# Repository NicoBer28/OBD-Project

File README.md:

# OBD-C

OBD-C is a car assistant and real-time analysis platform built around a
custom OBD-II Bluetooth dongle. A family (or a car-rental fleet) shares one
or more cars; the app tracks who's driving and where, splits fuel cost, and
surfaces real-time and historical vehicle data collected by the hardware.

## Features

- Division of fuel cost among multiple users
- Real-time vehicle diagnostics and driving-behavior feedback
- Fuel efficiency tracking, maintenance reminders and alerts
- Trip history and last-parked location
- Compatibility with a wide range of vehicles that support OBD-II

## Repository layout

This is a monorepo with three buildable pieces plus the hardware design:

| Path | What it is | Start here |
|---|---|---|
| `app/` | Flutter app (iOS/Android/desktop) — the user-facing client | [`app/obd_app/README.md`](app/obd_app/README.md) |
| `api/` | Spring Boot backend — auth, cars, groups, trips, telemetry | [`api/README.md`](api/README.md) · [`api/ROADMAP.md`](api/ROADMAP.md) |
| `hardware/` | ESP32 firmware — BLE + OBD-II/CAN bus reading | [`hardware/README.md`](hardware/README.md) |
| `circuito/` | KiCad schematic/PCB for the OBD dongle | — |

## Architecture at a glance

The Flutter UI is a "dumb" reactive layer: it doesn't touch Bluetooth or
GPS, it just listens to an event channel and draws. A native foreground
service (Kotlin on Android, Swift on iOS) owns the BLE/GPS connection and
survives the UI being killed, so a trip keeps recording with the phone in a
pocket. The ESP32 dongle only speaks BLE, so **the phone is the relay** —
it batches readings and uploads them to the API, which is built to make
retrying a batch always safe. Full reasoning: [`docs/architecture.md`](docs/architecture.md).
System diagram (Structurizr C4 model): [`docs/C4 diagram`](<docs/C4 diagram>).

## Getting started

- **App** — Flutter setup: [`app/obd_app/README.md`](app/obd_app/README.md).
  Building for iOS needs one extra per-developer step:
  [`docs/ios-setup.md`](docs/ios-setup.md).
- **API** — needs Postgres and a couple of env vars:
  [`api/README.md`](api/README.md).
- **Firmware** — ESP-IDF via Docker/Dev Containers:
  [`hardware/README.md`](hardware/README.md).

## Development workflow

- **Branching**: GitFlow — see [`docs/flow.md`](docs/flow.md).
- **Commits**: [Conventional Commits](https://www.conventionalcommits.org/),
  enforced by a `commit-msg` hook (`feat`, `fix`, `docs`, `chore`, …).
- **One-time setup**: `make setup` installs the git hooks (lefthook +
  `.githooks`).
- **Before pushing**: `make format` (dart + clang-format) and `make check`
  (format check, `flutter analyze`, `flutter test`).
- CI (`.github/workflows/ci.yaml`) currently only guards that `README.md`
  and `docs/` exist; extend it here as the app/firmware test suites grow
  (the API already runs its own suite via `./mvnw test`, see
  [`api/README.md`](api/README.md#testing)).

## Docs index

| Doc | Contents |
|---|---|
| [`docs/flow.md`](docs/flow.md) | Git branching model (GitFlow) |
| [`docs/architecture.md`](docs/architecture.md) | Architecture decisions and rationale — background telemetry, native bridge, Pigeon, BLE pitfalls |
| [`docs/funcionalities.md`](docs/funcionalities.md) | Feature brainstorm/spec: sharing, historical data, notifications, B2B |
| [`docs/C4 diagram`](<docs/C4 diagram>) | C4 model (Structurizr) of the system |
| [`docs/ios-setup.md`](docs/ios-setup.md) | Per-developer iOS signing setup, and how to build/run on iOS |

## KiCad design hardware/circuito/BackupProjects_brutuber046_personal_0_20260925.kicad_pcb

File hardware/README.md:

# OBD-Project: ESP32 Firmware
Entorno de desarrollo de firmware en ESP-IDF utilizando Docker y VS Code Dev Containers.

## ⚙️ Setup del Entorno en Linux

### 1. Instalar Docker y Visual Studio Code. 

- Se puede evitar este último, pero en ese caso hay que abrir una terminal dentro docker para compilar

### 2. Descargar la imagen oficial de espressif
```bash
docker pull espressif/idf:v6.1
```
### 3. Instalar la extensión Dev Containers en VS Code 
- Tambien llamada por ID `ms-vscode-remote.remote-containers`

### 4. Abrir la carpeta raíz del repositorio (OBD-Project) en VS Code

```bash
# desde el directorio previo al repositorio de git
code ./OBD-Project/
# o, desde dentro de OBD-Project
code .
```

### 5. Crear una carpeta llamada `.devcontainer` y adentro crear el archivo `devcontainer.json` con el siguiente contenido
```json
{
  "name": "ESP32 Lab",
  "image": "espressif/idf:latest",
  "runArgs": [
    "--network=host",
    "--privileged"
  ],
  "workspaceFolder": "/workspaces/OBD-Project/hardware",
  "mounts": [
    "source=/dev,target=/dev,type=bind"
  ],
  "customizations": {
    "vscode": {
      "extensions": [
        "ms-vscode.cpptools-extension-pack",
		"usernamehw.errorlens",
		"google.google-antigravity"
      ]
    }
  },
  "postCreateCommand": "echo 'source /opt/esp/idf/export.sh' >> ~/.bashrc"
}

```

### 6. Presionar F1, escribir Dev Containers: Reopen in Container y presionar Enter (o usar el botón inferior derecho).
- Se va a abrir dentro de la carpeta hardware, esto es para facilitar el workflow
## 🛠️ Build & Flash
### 1. Con el contenedor ya cargado, abrir una nueva terminal integrada en VS Code
- Se va a abrir una terminal dentro del contenedor

### 2. Seleccionar modelo de ESP y transceptor:
```bash
./set_driver.sh <transceptor> <modelo>
```
- Modelo puede ser `esp32`, `esp32-c3` o cualquier modelo compatible con las funcionalidades (tomar en cuenta la implementación en simple o multinúcleo de las tareas en FreeRTOS)
- Transceptor puede ser `twai` o `mcp`
### 3. Para compilar:
```bash
idf.py build
```
- Se van a descargar todas las dependencias del proyecto
### 4. La libreria del mcp2515 utilizada tiene un error de dependencias en su `CMakeLists.txt`. Para corregirlo ejecutar, desde el directorio actual:

```bash
echo "idf_component_register(SRCS "mcp2515.cpp"
                    INCLUDE_DIRS "include"
                    REQUIRES esp_driver_spi)" > ./managed_components/mcp2515/CMakeLists.txt
```
- Tambien se puede editar directamente el archivo
### 5. Flashear la ESP32 y abrir el monitor serial simultáneamente:

```bash
idf.py flash monitor
```
- (Para salir del monitor serial: `Ctrl + ]`)

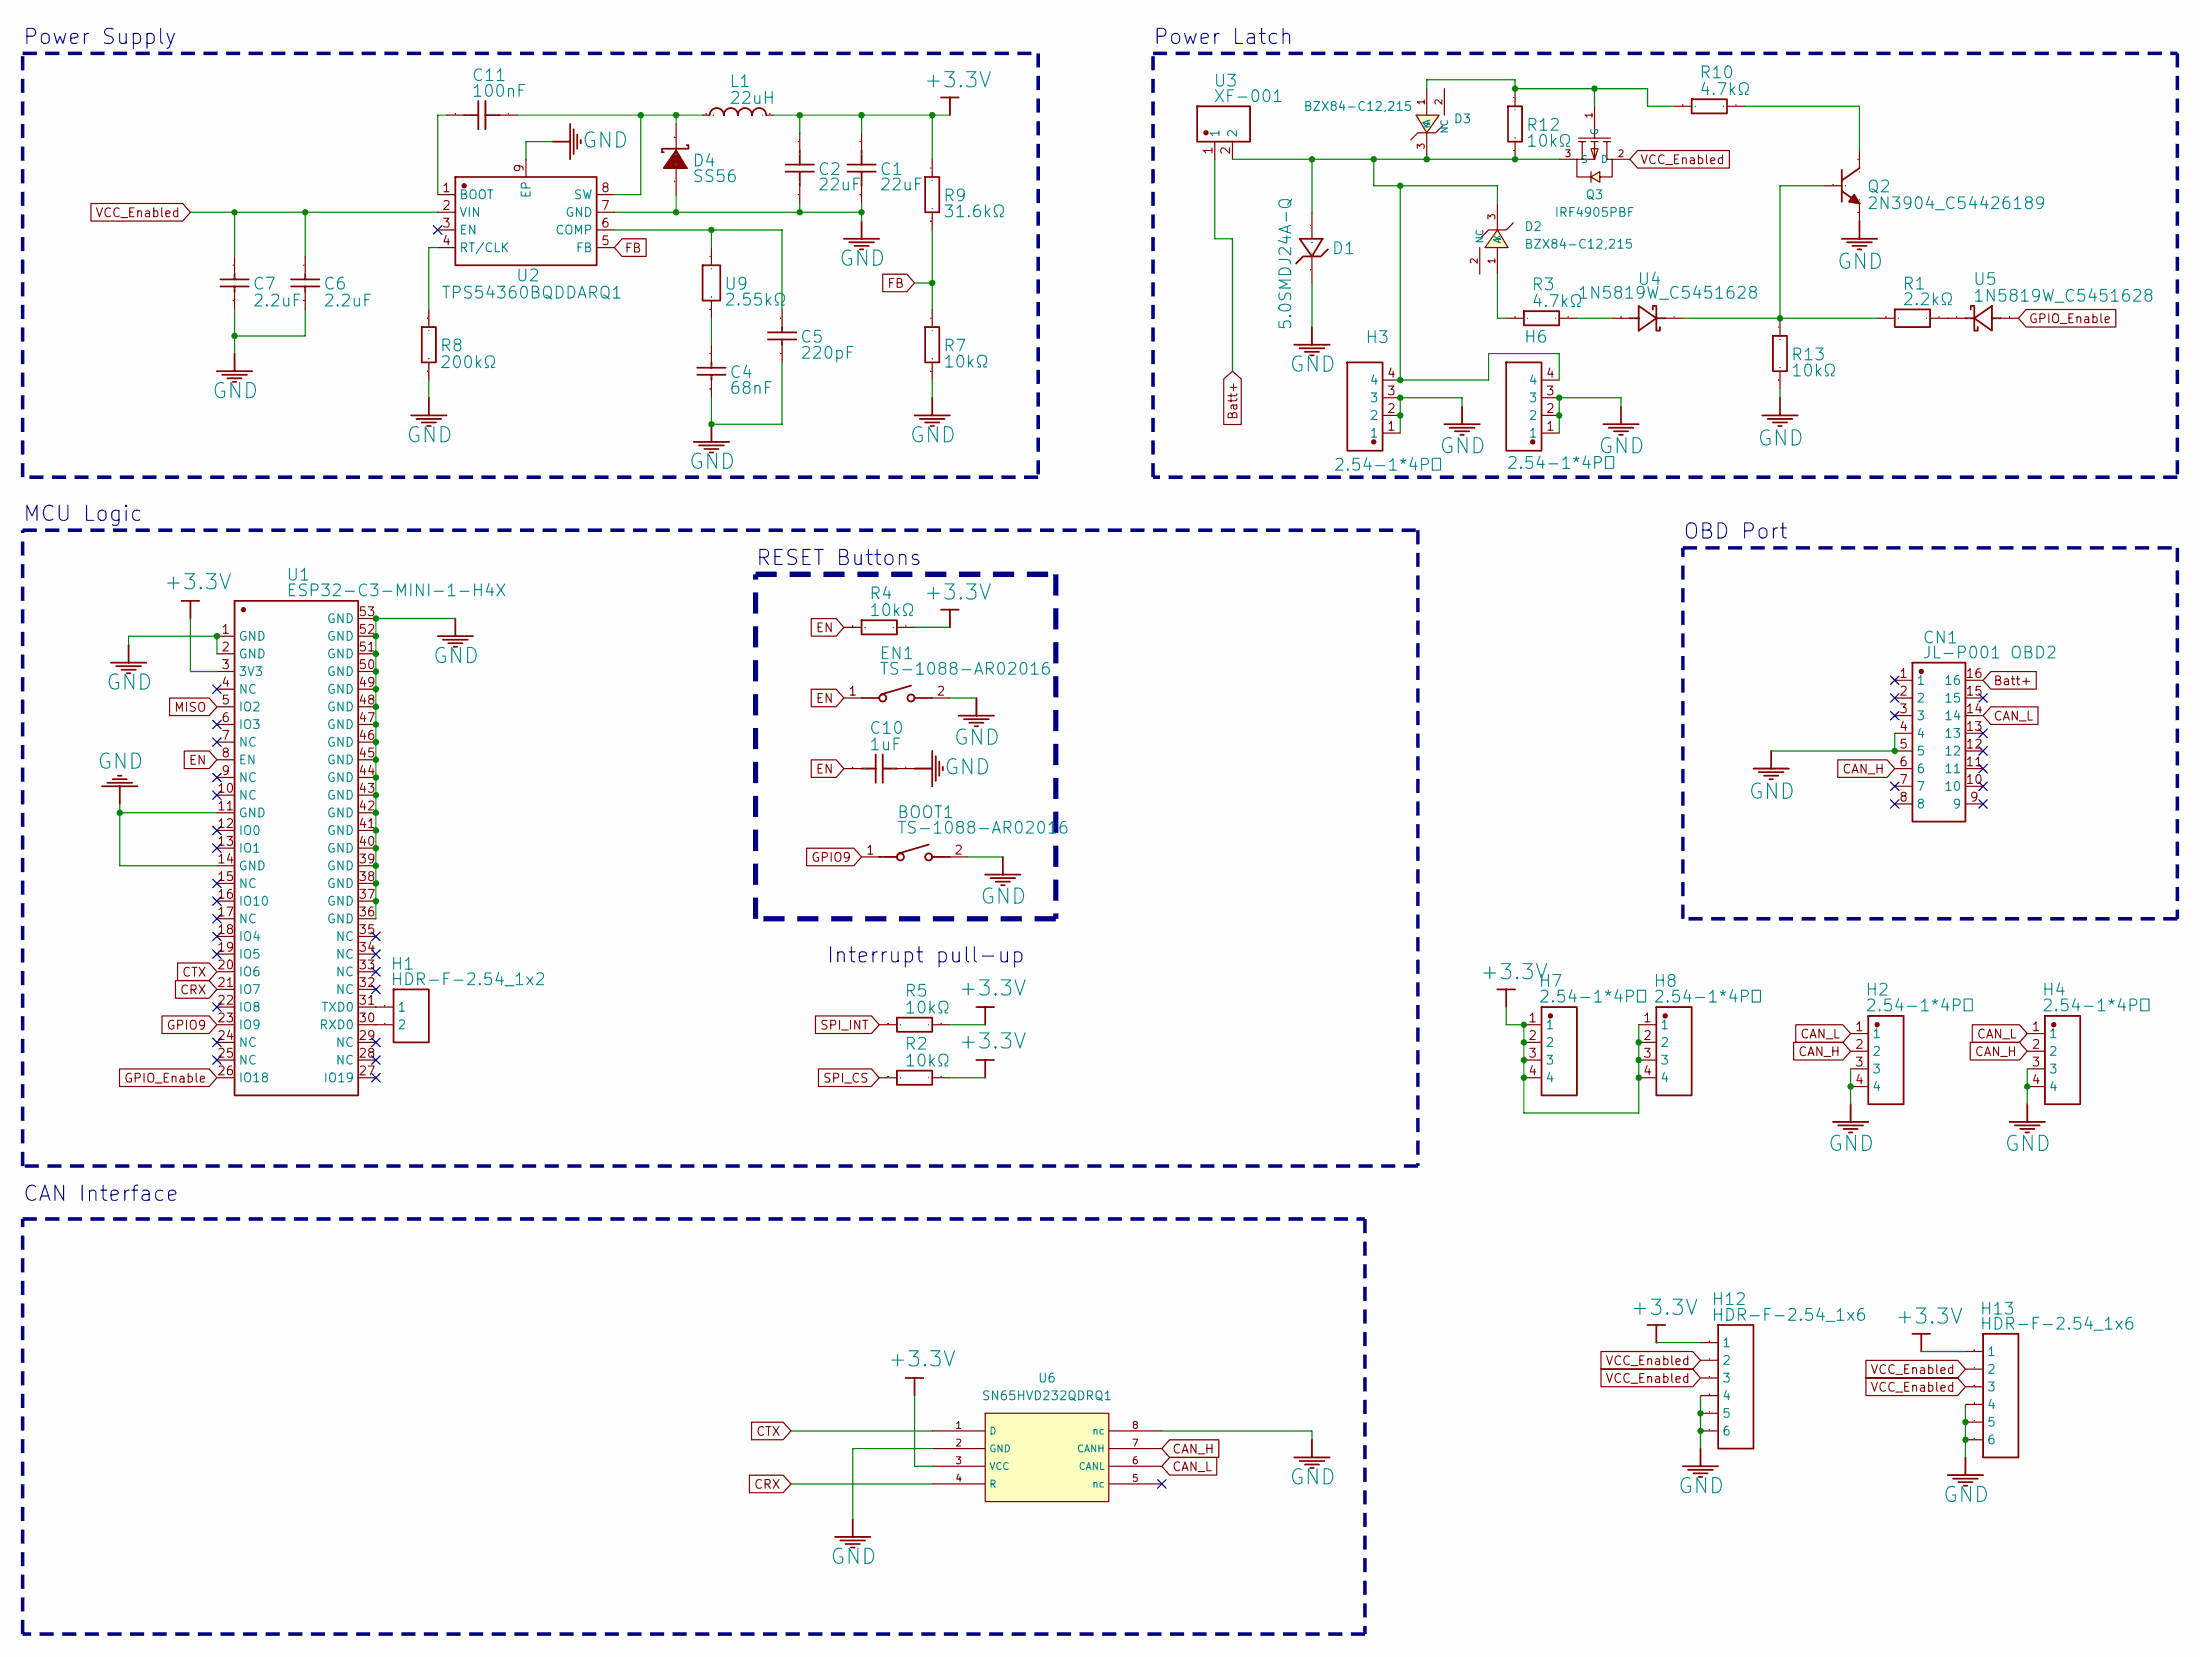
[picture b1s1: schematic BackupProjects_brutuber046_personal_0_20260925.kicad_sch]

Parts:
BOOT1: TS-1088-AR02016; C720477_SW-SMD_L3_9-W3_0-P4_45; Manufacturer Part TS-1088-AR02016
C1, C2: 22uF; C342620_C1206; Manufacturer Part C3216X5R1V226MTJ00E
C4: 68nF; C107098_C0603; Manufacturer Part CC0603KRX7R9BB683
C5: 220pF; C1603_C0603; Manufacturer Part CL10B221KB8NNNC
C6, C7: 2.2uF; C50254_C1206; Manufacturer Part CL31B225KBHNNNE
C10: 1uF; C1848_C1206; Manufacturer Part CL31B105KBHNNNE
C11: 100nF; C14663_C0603; Manufacturer Part CC0603KRX7R9BB104
CN1: JL-P001 OBD2; C9900237086_CONN-SMD_16P-P4_00_ODB16PIN; Manufacturer Part JL-P001 OBD2
D1: 5.0SMDJ24A-Q; C362107_SMC_L7_2-W5_8-LS7_9-RD; Manufacturer Part SMDJ24A
D2, D3: BZX84-C12,215; C108437_SOT-23_L2_9-W1_3-P1_90-LS2_4-BR; LCSC C108437
D4: SS56; C65009_SMA_L4_3-W2_6-LS5_2-RD; Manufacturer Part SS56
EN1: TS-1088-AR02016; C720477_SW-SMD_L3_9-W3_0-P4_45; Manufacturer Part TS-1088-AR02016
H1: HDR-F-2.54_1x2; C49661_HDR-TH_2P-P2_54-V-F
H2, H3, H4, H6, H7, H8: 2.54-1*4P母; C2718488_HDR-TH_4P-P2_54-V-F; Manufacturer Part 2.54-1*4P母
H12, H13: HDR-F-2.54_1x6; C40877_HDR-TH_6P-P2_54-V-F
L1: 22uH; C52196365_IND-SMD_L12_5-W12_5; Manufacturer Part GXDR1207-220MT
Q2: 2N3904_C54426189; C54426189_TO-92-3_L4_9-W3_7-P2_54-L; Manufacturer Part 2N3904
Q3: IRF4905PBF; C2564_TO-220-3_L10_0-W4_5-P2_54-T; LCSC C2564
R1: 2.2kΩ; C2907234_R0805; Manufacturer Part FRC0805F2201TS
R2, R4, R5, R7, R12, R13: 10kΩ; C17902_R1206; Manufacturer Part 1206W4F1002T5E
R3, R10: 4.7kΩ; C17673_R0805; Manufacturer Part 0805W8F4701T5E
R8: 200kΩ; C17539_R0805; Manufacturer Part 0805W8F2003T5E
R9: 31.6kΩ; C185339_R0603; Manufacturer Part RC0603FR-0731K6L
U1: ESP32-C3-MINI-1-H4X; C41349510_WIFIM-SMD_ESP32-C3-MINI-1; Manufacturer Part ESP32-C3-MINI-1-H4X
U2: TPS54360BQDDARQ1; C2687968_SO-8_L4_9-W3_9-P1_27-LS6_0-BL-EP; Manufacturer Part TPS54360BQDDARQ1
U3: XF-001; C17700140_CONN-TH_XF-001; Manufacturer Part XF-001
U4, U5: 1N5819W_C5451628; C5451628_SOD-123_L2_7-W1_6-LS3_7-FD; Manufacturer Part 1N5819W
U6: SN65HVD232QDRQ1; C130019_SOIC-8_L4_9-W3_9-P1_27-LS6_0-BL; LCSC C130019
U9: 2.55kΩ; C2930415_R1206; Manufacturer Part FRC1206F2551TS

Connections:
+3.3V: C1.2, C2.2, H7.1, H7.2, H7.3, H7.4, H8.1, H8.2, H8.3, H8.4, H12.1, H13.1, L1.2, R2.2, R4.2, R5.2, R9.2, U1.3 (3V3), U6.3 (VCC)
Batt+: CN1.16, U3.1
CAN_H: CN1.6, H2.2, H4.2, U6.7 (CANH)
CAN_L: CN1.14, H2.1, H4.1, U6.6 (CANL)
CRX: U1.21 (IO7), U6.4 (R)
CTX: U1.20 (IO6), U6.1 (D)
EN: C10.1, EN1.1, R4.1, U1.8 (EN)
FB: R7.2, R9.1, U2.5 (FB)
GND: BOOT1.2, C1.1, C2.1, C4.1, C5.1, C6.1, C7.1, C10.2, CN1.4, CN1.5, D1.1 (C), D4.2 (A), EN1.2, H2.3, H2.4, H3.1, H3.2, H3.3, H4.3, H4.4, H6.1, H6.2, H6.3, H12.4, H12.5, H12.6, H13.4, H13.5, H13.6, Q2.1 (E), R7.1, R8.1, R13.1, U1.1 (GND), U1.2 (GND), U1.11 (GND), U1.14 (GND), U1.36 (GND), U1.37 (GND), U1.38 (GND), U1.39 (GND), U1.40 (GND), U1.41 (GND), U1.42 (GND), U1.43 (GND), U1.44 (GND), U1.45 (GND), U1.46 (GND), U1.47 (GND), U1.48 (GND), U1.49 (GND), U1.50 (GND), U1.51 (GND), U1.52 (GND), U1.53 (GND), U2.7 (GND), U2.9 (EP), U6.2 (GND), U6.8 (nc)
GPIO9: BOOT1.1, U1.23 (IO9)
GPIO_Enable: U1.26 (IO18), U5.1 (A)
MISO: U1.5 (IO2)
unnamed: C4.2, U9.1
unnamed: D1.2 (A), D2.3 (K), D3.3 (K), H3.4, H6.4, Q3.3 (S), R12.1, U3.2
unnamed: D2.1 (A), R3.1
unnamed: D3.1 (A), Q3.1 (G), R10.1, R12.2
unnamed: C11.2, D4.1 (K), L1.1, U2.8 (SW)
unnamed: Q2.2 (B), R1.1, R13.2, U4.2 (K)
unnamed: Q2.3 (C), R10.2
unnamed: H1.2, U1.30 (RXD0)
unnamed: H1.1, U1.31 (TXD0)
unnamed: C11.1, U2.1 (BOOT)
unnamed: C5.2, U2.6 (COMP), U9.2
unnamed: R8.2, U2.4 (RT/CLK)
unnamed: R3.2, U4.1 (A)
unnamed: R1.2, U5.2 (K)
SPI_CS: R2.1
SPI_INT: R5.1
VCC_Enabled: C6.2, C7.2, H12.2, H12.3, H13.2, H13.3, Q3.2 (D), U2.2 (VIN)

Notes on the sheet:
Power Latch
Interrupt pull-up
MCU Logic
OBD Port
CAN Interface
RESET Buttons
Power Supply

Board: 2 copper layers, 45 parts (1 on the bottom side), 26 nets, no tracks yet.
